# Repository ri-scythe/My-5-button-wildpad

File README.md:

# wildpad
A custom 5 button macropad built for the Hack Club Hackpad project. It features 2 layers for shortcuts and gifs, 5 keycaps, OLED screen and a rotary encoder. 

# CAD

# PCB
Created in KiCad.

PCB 

Schematic

# Firmware
This macropad uses [QMK](https://qmk.fm/) firmware.

- The rotary encoder changes volume.
- The 4 keys on the first layer are used to open apps and turn on bluetooth, the same 4 keys display different GIFS on OLED, and 1 of the keys is for changing the layer.

# BOM

- 5x Cherry MX Switches
- 5x DSA Keycaps
- 4x M3x5x4 Heatset inserts
- 4x M3x16mm Screws
- 1x EC11 Rotary Encoder
- 1x 0.91" OLED Display
- 1x Seeed Studio XIAO RP2040
- 5x SK6812 MINI LEDs
- 6x Through-hole 1N4148 Diodes
- 1x Case(2 separate parts)
- 1x Soldering Iron

# Fun fact

i actually had a black bunny

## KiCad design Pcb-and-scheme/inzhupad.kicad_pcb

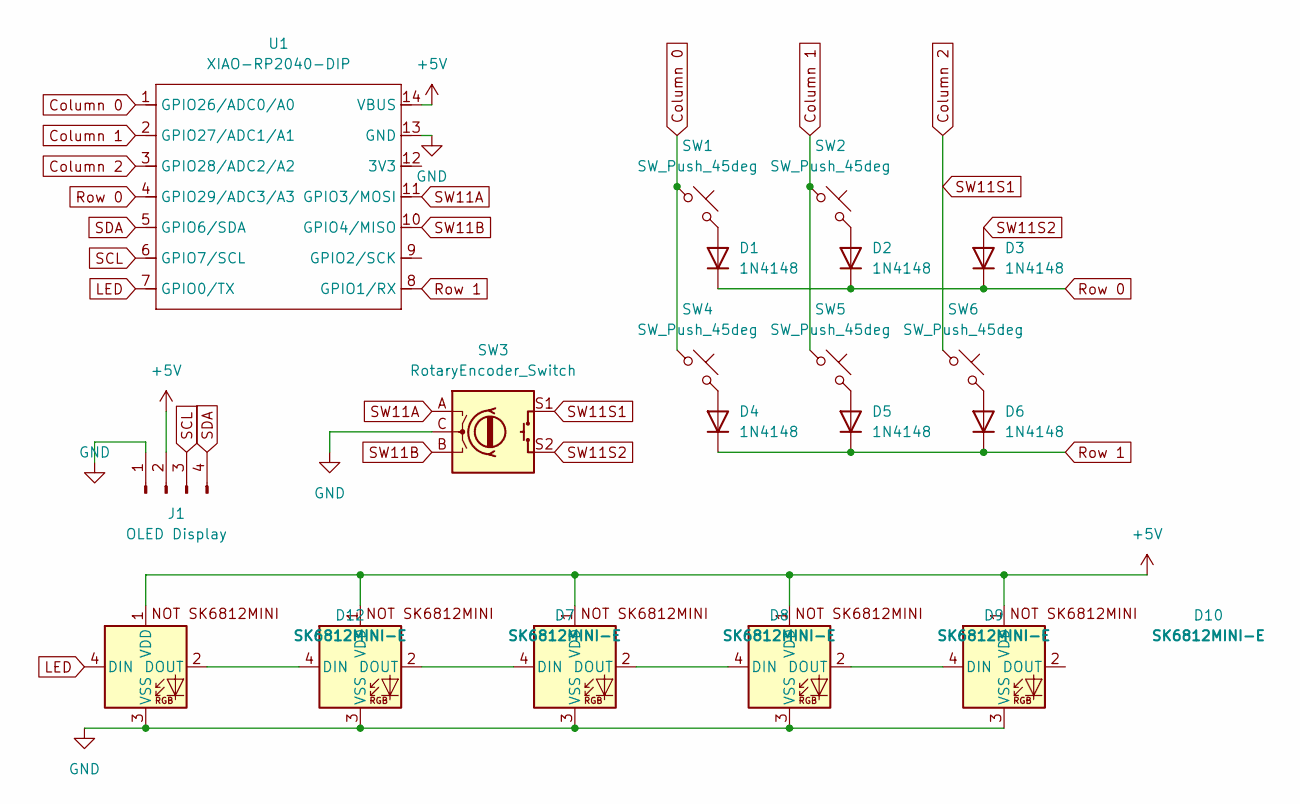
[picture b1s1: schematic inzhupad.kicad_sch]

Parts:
D1, D2, D3, D4, D5, D6: 1N4148; D_DO-35_SOD27_P7.62mm_Horizontal
D7, D8, D9, D10, D12: SK6812MINI-E; SK6812MINI-E_fixed
J1: OLED Display; PinHeader_1x04_P2.54mm_Vertical
SW1, SW2, SW4, SW5, SW6: SW_Push_45deg; SW_Cherry_MX_1.00u_PCB
SW3: RotaryEncoder_Switch; RotaryEncoder_Alps_EC11E-Switch_Vertical_H20mm
U1: XIAO-RP2040-DIP

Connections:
+5V: D7.1 (VDD), D8.1 (VDD), D9.1 (VDD), D10.1 (VDD), D12.1 (VDD), J1.2, U1.14 (VBUS)
Column 0: SW1.1, SW4.1, U1.1 (GPIO26/ADC0/A0)
Column 1: SW2.1, SW5.1, U1.2 (GPIO27/ADC1/A1)
Column 2: SW3.S1, SW6.1, U1.3 (GPIO28/ADC2/A2)
GND: D7.3 (VSS), D8.3 (VSS), D9.3 (VSS), D10.3 (VSS), D12.3 (VSS), J1.1, SW3.C, U1.13 (GND)
LED: D12.4 (DIN), U1.7 (GPIO0/TX)
unnamed: D1.2 (A), SW1.2
unnamed: D2.2 (A), SW2.2
unnamed: D4.2 (A), SW4.2
unnamed: D5.2 (A), SW5.2
unnamed: D6.2 (A), SW6.2
unnamed: D7.2 (DOUT), D8.4 (DIN)
unnamed: D8.2 (DOUT), D9.4 (DIN)
unnamed: D9.2 (DOUT), D10.4 (DIN)
unnamed: D7.4 (DIN), D12.2 (DOUT)
Row 0: D1.1 (K), D2.1 (K), D3.1 (K), U1.4 (GPIO29/ADC3/A3)
Row 1: D4.1 (K), D5.1 (K), D6.1 (K), U1.8 (GPIO1/RX)
SCL: J1.3, U1.6 (GPIO7/SCL)
SDA: J1.4, U1.5 (GPIO6/SDA)
SW11A: SW3.A, U1.11 (GPIO3/MOSI)
SW11B: SW3.B, U1.10 (GPIO4/MISO)
SW11S2: D3.2 (A), SW3.S2

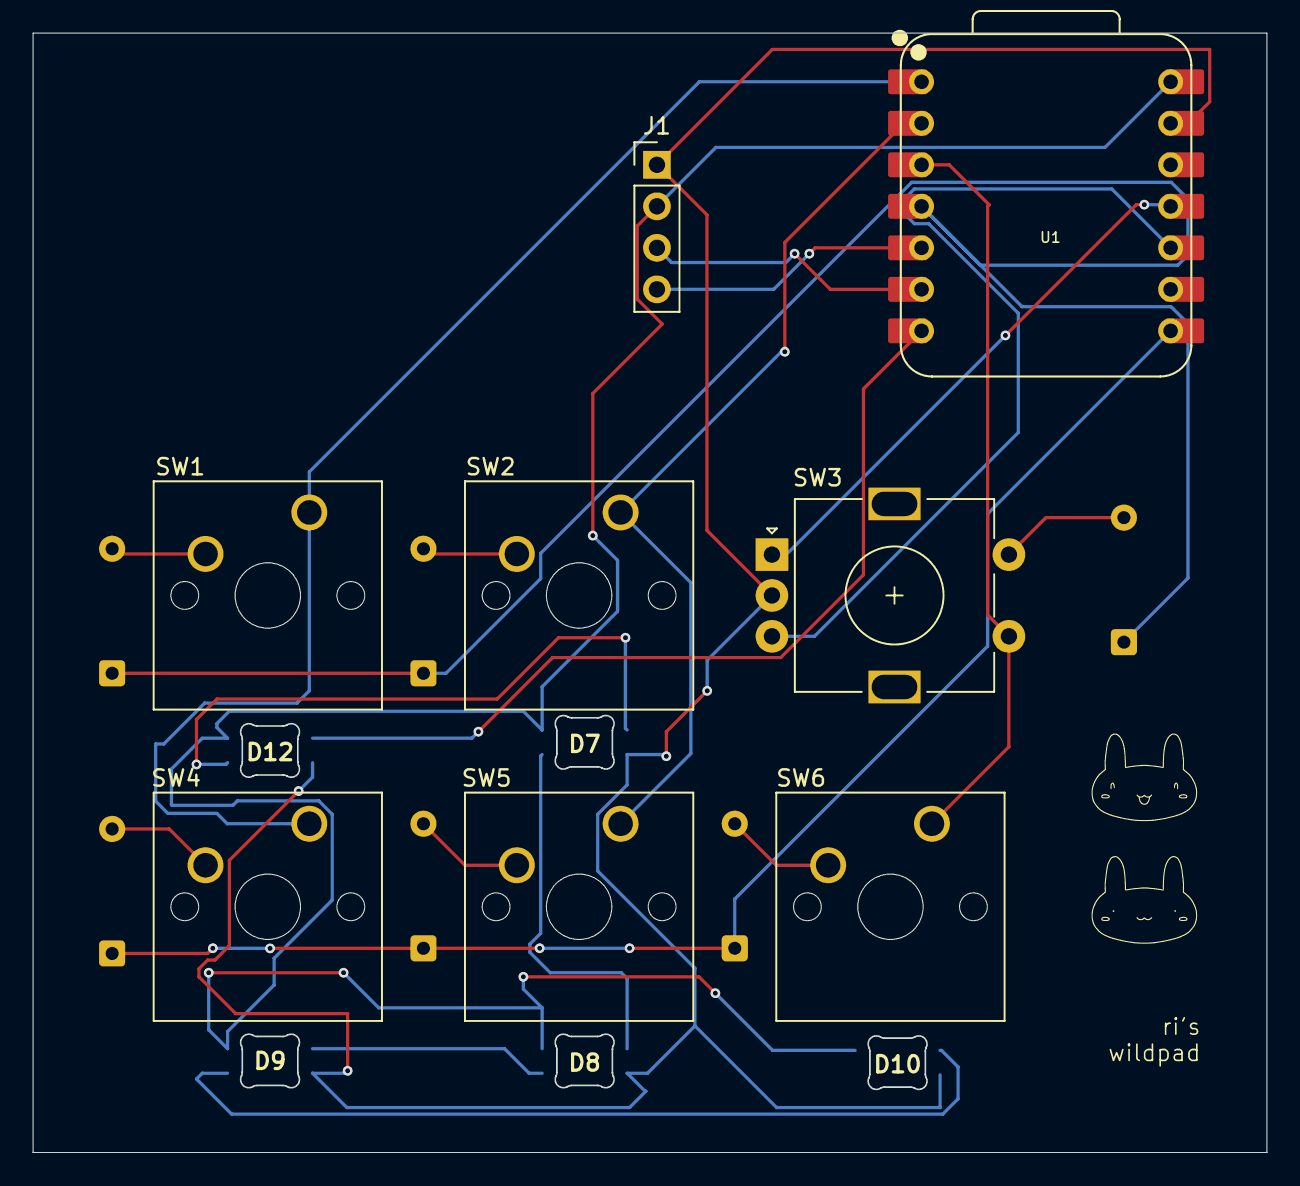
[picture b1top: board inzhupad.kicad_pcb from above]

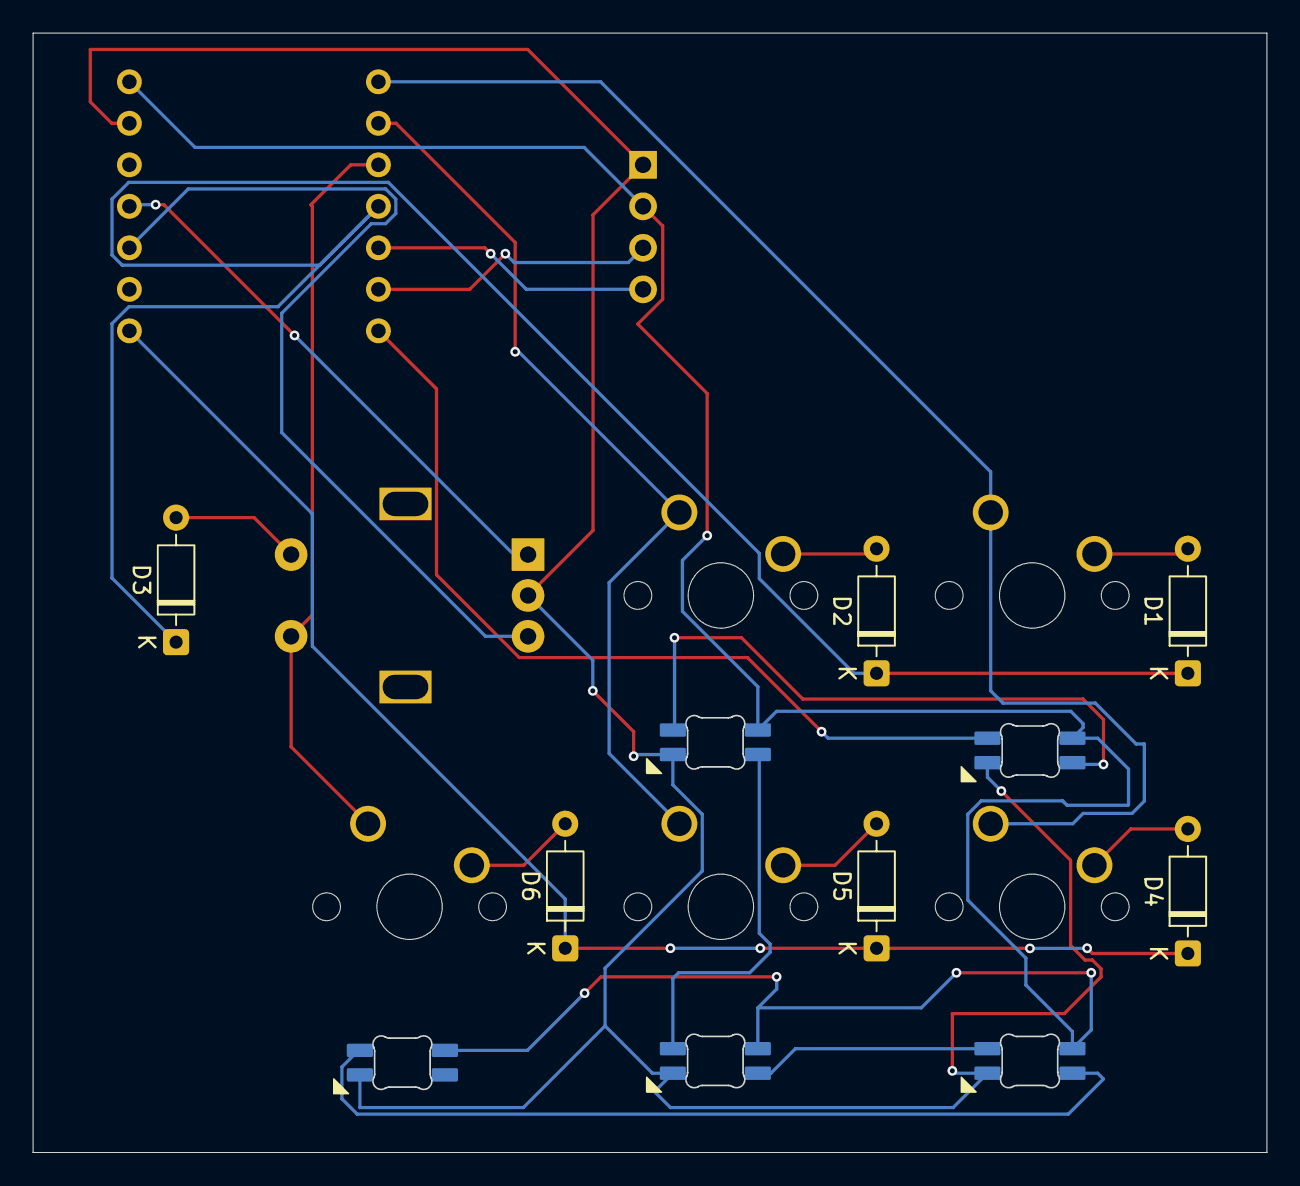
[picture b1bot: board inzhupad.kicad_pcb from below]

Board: 2 copper layers, 75.5 x 68.5 mm, 19 parts (6 on the bottom side), 22 nets.

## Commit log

2026-03-01 Update README with new features and components
2026-03-01 Revise README with project details and sections
    Updated project name and added detailed sections for CAD, PCB, Firmware, BOM, and Extra information.
2026-03-01 Enhance README with CAD and PCB details
    Added images and sections for CAD, PCB, and Schematic.
2026-03-19 Create O
2026-03-19 Remove soldering iron from README components list
    Removed mention of soldering iron from the components list.
2026-03-19 Create s
2026-03-20 Create A
